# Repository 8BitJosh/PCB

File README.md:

# PCB
Collection of PCB Designs

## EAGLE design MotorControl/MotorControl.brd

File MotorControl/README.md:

Board designed to control the speed and driection of two motors from a 12V lead-acid battery

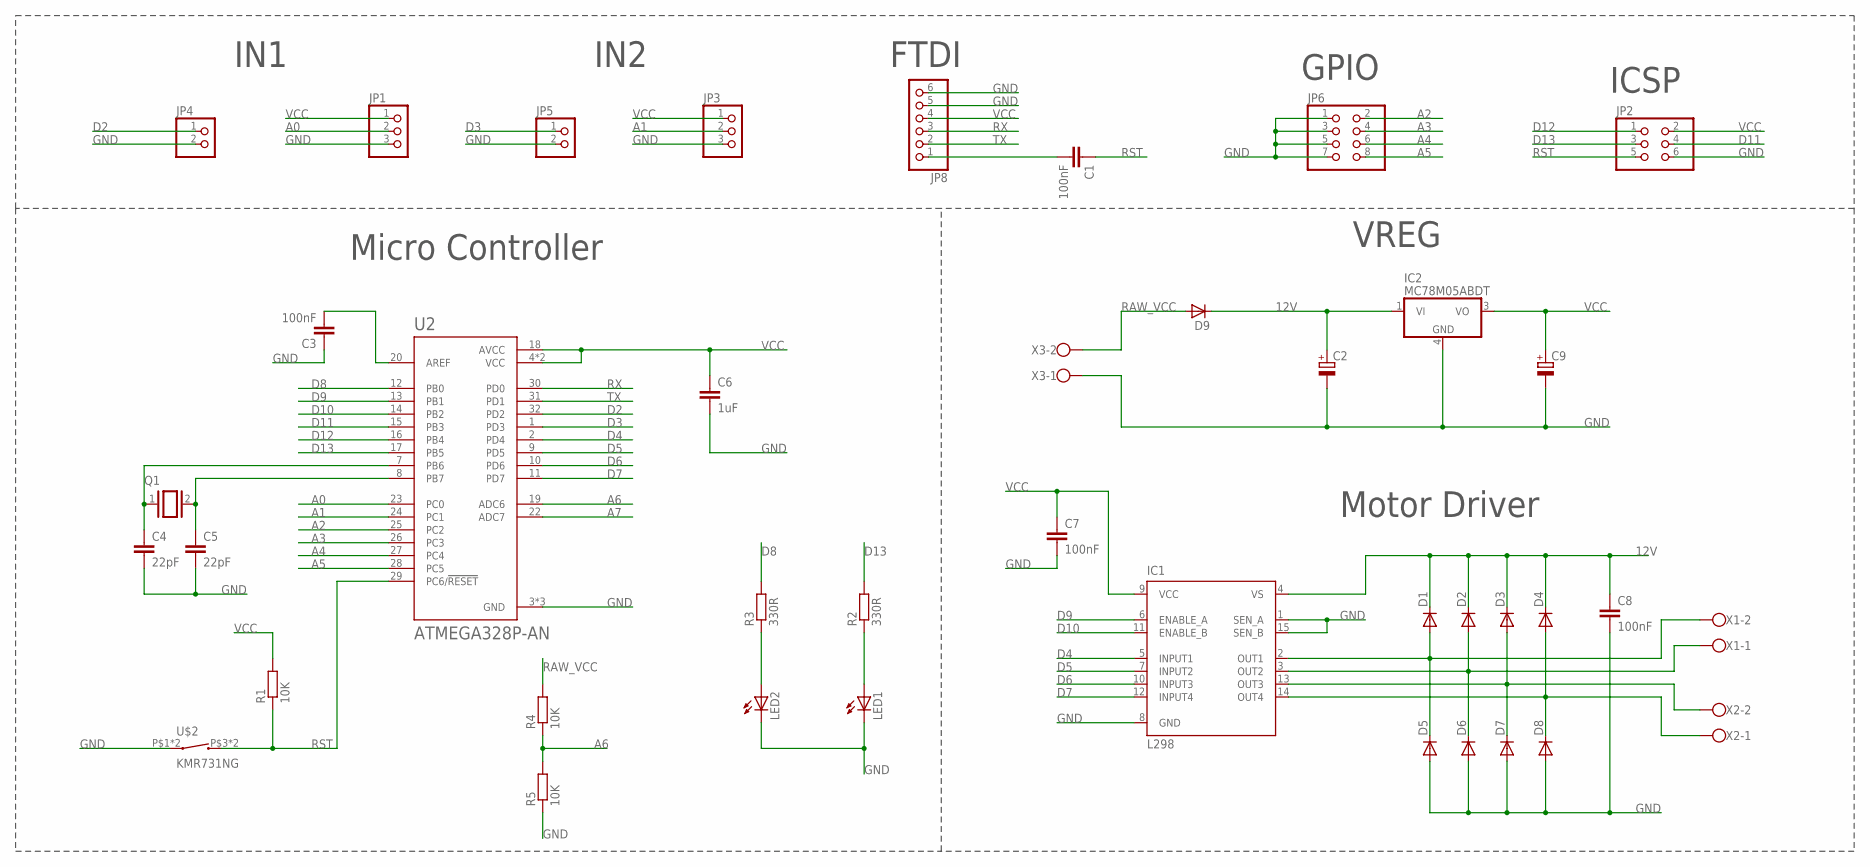
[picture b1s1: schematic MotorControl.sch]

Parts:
C1, C3, C7, C8: 100nF; C1206
C2, C9: CPOL-EU140CLH-0810; 140CLH-0810
C4, C5: 22pF; C1206
C6: 1uF; C1206
D1, D2, D3, D4, D5, D6, D7, D8: DIODE-DO214AC; DO214AC
D9: DIODE_E-SMC; DIODE_SMC
IC1: L298; MULTIWATT-15
IC2: MC78M05ABDT; DPACK_3
JP1, JP3: PINHD-1X3; 1X03
JP2: PINHD-2X3; 2X03
JP4, JP5: PINHD-1X2; 1X02
JP6: PINHD-2X4; 2X04
JP8: PINHD-1X6; 1X06
LED1: LED_ESML0603; LED_SML0603
LED2: LED3MM
Q1: XTAL/S; QS
R1, R4, R5: 10K; R2012
R2, R3: 330R; R2012
U2: ATMEGA328P-AN; QFP80P900X900X120-32N
U$2: KMR731NG
X1, X2, X3: W237-102

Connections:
12V: C2.+, C8.1, D1.C, D2.C, D3.C, D4.C, D9.C (A), IC1.4 (VS), IC2.1 (VI)
A0: JP1.2, U2.23 (PC0)
A1: JP3.2, U2.24 (PC1)
A2: JP6.2, U2.25 (PC2)
A3: JP6.4, U2.26 (PC3)
A4: JP6.6, U2.27 (PC4)
A5: JP6.8, U2.28 (PC5)
A6: R4.1, R5.2, U2.19 (ADC6)
A7: U2.22 (ADC7)
D2: JP4.1, U2.32 (PD2)
D3: JP5.1, U2.1 (PD3)
D4: IC1.5 (INPUT1), U2.2 (PD4)
D5: IC1.7 (INPUT2), U2.9 (PD5)
D6: IC1.10 (INPUT3), U2.10 (PD6)
D7: IC1.12 (INPUT4), U2.11 (PD7)
D8: R3.2, U2.12 (PB0)
D9: IC1.6 (ENABLE_A), U2.13 (PB1)
D10: IC1.11 (ENABLE_B), U2.14 (PB2)
D11: JP2.4, U2.15 (PB3)
D12: JP2.1, U2.16 (PB4)
D13: JP2.3, R2.2, U2.17 (PB5)
GND: C2.-, C3.1, C4.2, C5.2, C6.2, C7.2, C8.2, C9.-, D5.A, D6.A, D7.A, D8.A, IC1.1 (SEN_A), IC1.8 (GND), IC1.15 (SEN_B), IC2.4 (GND), JP1.3, JP2.6, JP3.3, JP4.2, JP5.2, JP6.1, JP6.3, JP6.5, JP6.7, JP8.5, JP8.6, LED1.C, LED2.K (C), R5.1, U2.3 (GND), U2.5 (GND), U2.21 (GND), U$2.P$1 (1), U$2.P$2 (1), X3.1
unnamed: D1.A, D5.C, IC1.2 (OUT1), X1.2
unnamed: C4.1, Q1.1, U2.7 (PB6)
unnamed: C3.2, U2.20 (AREF)
unnamed: C5.1, Q1.2, U2.8 (PB7)
unnamed: LED1.A, R2.1
unnamed: LED2.A, R3.1
unnamed: D2.A, D6.C, IC1.3 (OUT2), X1.1
unnamed: D3.A, D7.C, IC1.13 (OUT3), X2.2
unnamed: D4.A, D8.C, IC1.14 (OUT4), X2.1
unnamed: C1.2, JP8.1
RAW_VCC: D9.A (C), R4.2, X3.2
RST: C1.1, JP2.5, R1.1, U2.29 (PC6/!RESET), U$2.P$3 (2), U$2.P$4 (2)
RX: JP8.3, U2.30 (PD0)
TX: JP8.2, U2.31 (PD1)
VCC: C6.1, C7.1, C9.+, IC1.9 (VCC), IC2.3 (VO), JP1.1, JP2.2, JP3.1, JP8.4, R1.2, U2.4 (VCC), U2.6 (VCC), U2.18 (AVCC)

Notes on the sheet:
IN1
IN2
GPIO
ICSP
Motor Driver
Micro Controller
FTDI
VREG

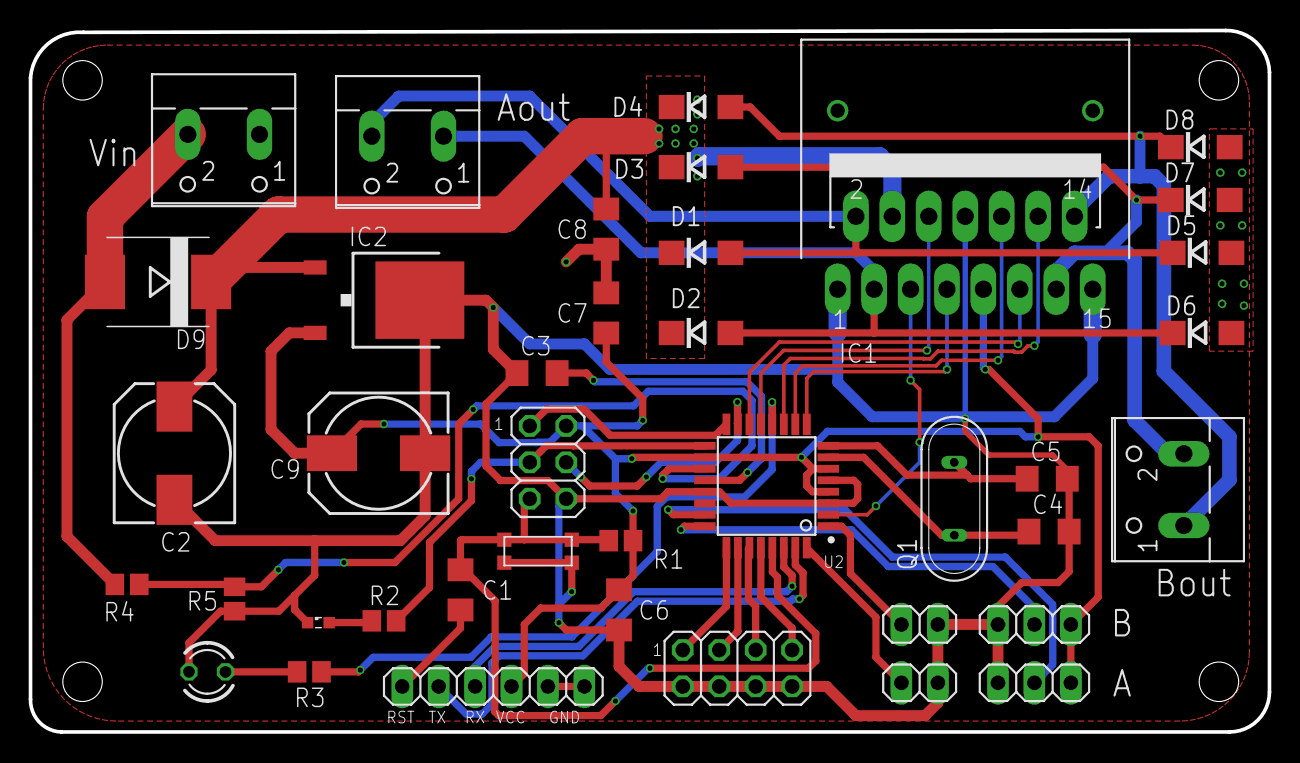
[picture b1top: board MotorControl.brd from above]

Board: 2 copper layers, 86.4 x 48.9 mm, 40 parts (0 on the bottom side), 36 nets.

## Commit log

2018-12-16 Initial libs
2018-12-16 MotorControl board
